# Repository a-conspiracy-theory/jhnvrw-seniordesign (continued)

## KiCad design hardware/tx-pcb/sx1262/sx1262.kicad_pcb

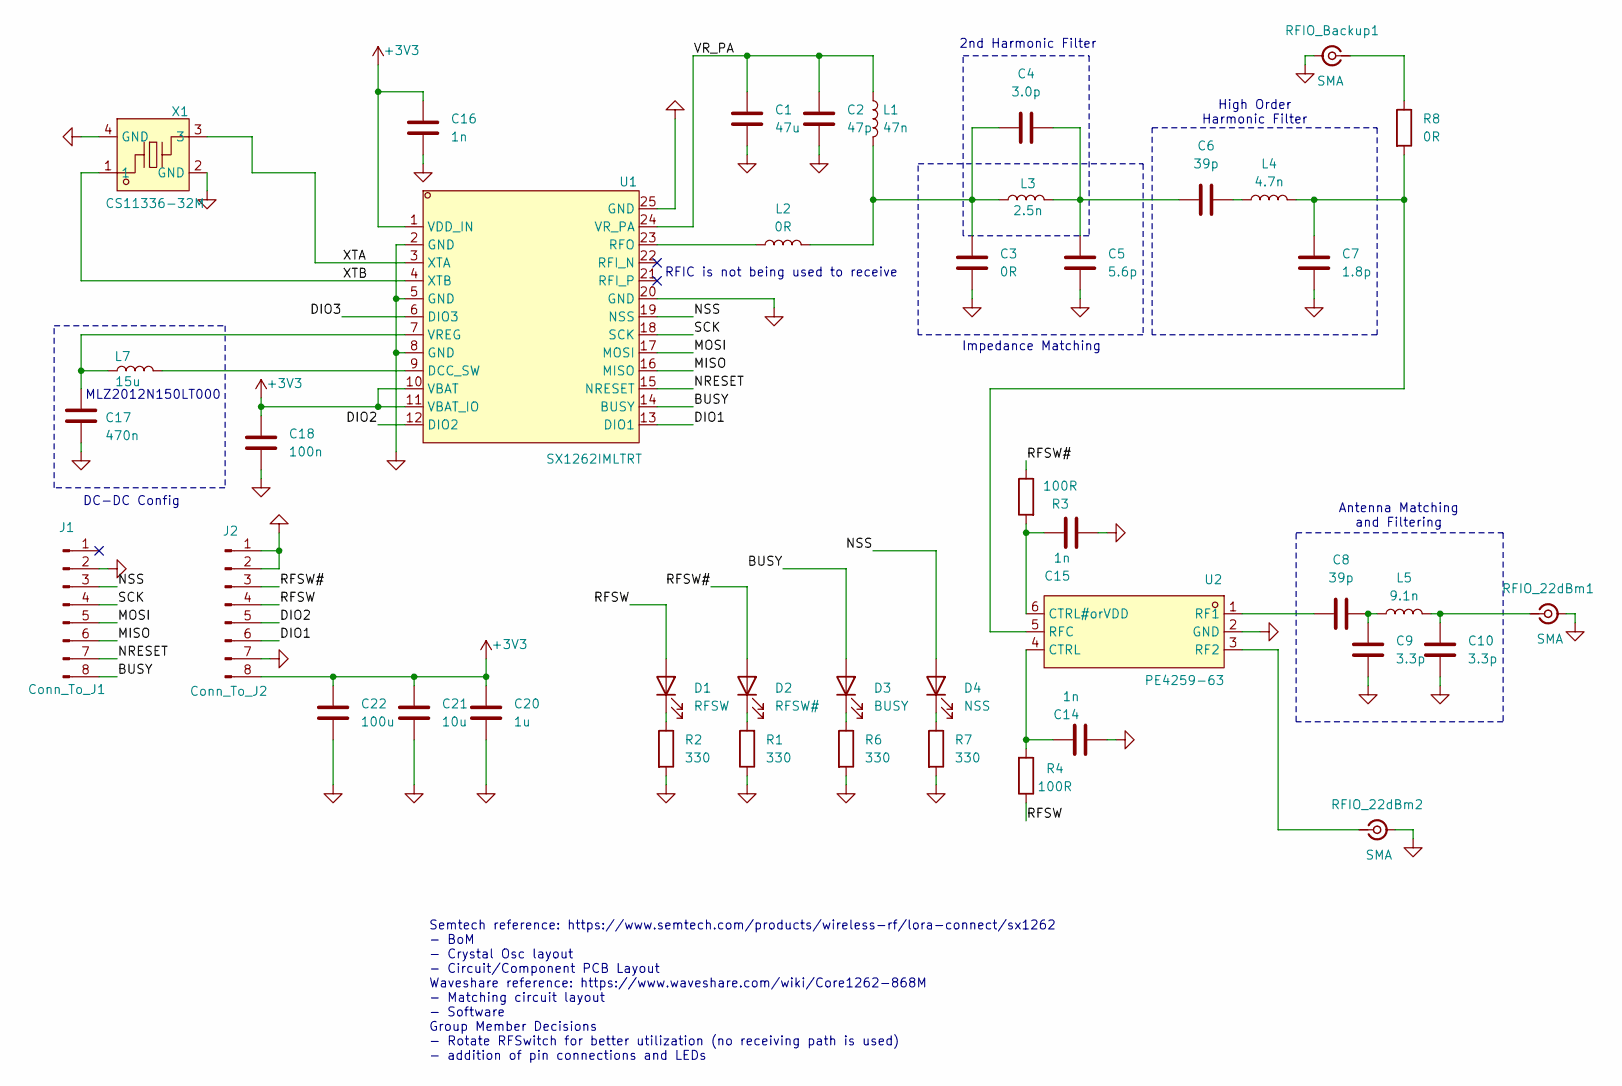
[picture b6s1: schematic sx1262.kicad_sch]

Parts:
C1: 47u; C_0805_2012Metric_Pad1.18x1.45mm_HandSolder
C2: 47p; C_0805_2012Metric_Pad1.18x1.45mm_HandSolder
C3: 0R; C_0805_2012Metric_Pad1.18x1.45mm_HandSolder
C4: 3.0p; C_0805_2012Metric_Pad1.18x1.45mm_HandSolder
C5: 5.6p; C_0805_2012Metric_Pad1.18x1.45mm_HandSolder
C6, C8: 39p; C_0805_2012Metric_Pad1.18x1.45mm_HandSolder
C7: 1.8p; C_0805_2012Metric_Pad1.18x1.45mm_HandSolder
C9, C10: 3.3p; C_0805_2012Metric_Pad1.18x1.45mm_HandSolder
C14, C15, C16: 1n; C_0805_2012Metric_Pad1.18x1.45mm_HandSolder
C17: 470n; C_0805_2012Metric_Pad1.18x1.45mm_HandSolder
C18: 100n; C_0805_2012Metric_Pad1.18x1.45mm_HandSolder
C20: 1u; C_0805_2012Metric_Pad1.18x1.45mm_HandSolder
C21: 10u; C_0805_2012Metric_Pad1.18x1.45mm_HandSolder
C22: 100u; C_0805_2012Metric_Pad1.18x1.45mm_HandSolder
D1: RFSW; LED_0805_2012Metric_Pad1.15x1.40mm_HandSolder
D2: RFSW#; LED_0805_2012Metric_Pad1.15x1.40mm_HandSolder
D3: BUSY; LED_0805_2012Metric_Pad1.15x1.40mm_HandSolder
D4: NSS; LED_0805_2012Metric_Pad1.15x1.40mm_HandSolder
J1: Conn_To_J1; PinHeader_1x08_P2.54mm_Vertical
J2: Conn_To_J2; PinHeader_1x08_P2.54mm_Vertical
L1: 47n; L_0805_2012Metric_Pad1.05x1.20mm_HandSolder
L2: 0R; L_0805_2012Metric_Pad1.05x1.20mm_HandSolder
L3: 2.5n; L_0805_2012Metric_Pad1.05x1.20mm_HandSolder
L4: 4.7n; L_0805_2012Metric_Pad1.05x1.20mm_HandSolder
L5: 9.1n; L_0805_2012Metric_Pad1.05x1.20mm_HandSolder
L7: 15u; L_0805_2012Metric_Pad1.05x1.20mm_HandSolder
R1, R2, R6, R7: 330; R_0805_2012Metric_Pad1.20x1.40mm_HandSolder
R3, R4: 100R; R_0805_2012Metric_Pad1.20x1.40mm_HandSolder
R8: 0R; R_0805_2012Metric_Pad1.20x1.40mm_HandSolder
RFIO_22dBm1, RFIO_22dBm2: SMA; SMA_Amphenol_901-143_Horizontal
RFIO_Backup1: SMA; SMA_Amphenol_901-143_Horizontal
U1: SX1262IMLTRT; QFN-24_L4.0-W4.0-P0.50-BL-EP2.6; MPN SX1262IMLTRT; LCSC Part C191341
U2: PE4259-63; SC-70-6_L2.2-W1.3-P0.65-LS2.1-BL; MPN PE4259-63; LCSC Part C470892
X1: CS11336-32M; NX2016SA_NDK; MPN Q22FA12800025; LCSC Part C187794

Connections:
+3V3: C16.1, C18.1, C20.1, C21.1, C22.1, J2.8, U1.1 (VDD_IN), U1.10 (VBAT), U1.11 (VBAT_IO)
/BUSY: D3.2 (A), J1.8, U1.14 (BUSY)
/DIO1: J2.6, U1.13 (DIO1)
/DIO2: J2.5, U1.12 (DIO2)
/DIO3: U1.6 (DIO3)
/MISO: J1.6, U1.16 (MISO)
/MOSI: J1.5, U1.17 (MOSI)
/NRESET: J1.7, U1.15 (NRESET)
/NSS: D4.2 (A), J1.3, U1.19 (NSS)
/RFSW: D1.2 (A), J2.4, R4.1
/RFSW#: D2.2 (A), J2.3, R3.1
/SCK: J1.4, U1.18 (SCK)
/VR_PA: C1.1, C2.1, L1.1, U1.24 (VR_PA)
/XTA: U1.3 (XTA), X1.3
/XTB: U1.4 (XTB), X1.1
GND: C1.2, C2.2, C3.2, C5.2, C7.2, C9.2, C10.2, C14.2, C15.2, C16.2, C17.2, C18.2, C20.2, C21.2, C22.2, J1.2, J2.1, J2.2, J2.7, R1.1, R2.2, R6.2, R7.2, RFIO_22dBm1.2 (Ext), RFIO_22dBm2.2 (Ext), RFIO_Backup1.2 (Ext), U1.2 (GND), U1.5 (GND), U1.8 (GND), U1.20 (GND), U1.25 (GND), U2.2 (GND), X1.2 (GND), X1.4 (GND)
unnamed: C3.1, C4.1, L1.2, L2.2, L3.1
unnamed: C4.2, C5.1, C6.1, L3.2
unnamed: C6.2, L4.1
unnamed: C8.2, C9.1, L5.1
unnamed: D1.1 (K), R2.1
unnamed: D2.1 (K), R1.2
unnamed: D3.1 (K), R6.1
unnamed: D4.1 (K), R7.1
unnamed: C10.1, L5.2, RFIO_22dBm1.1 (In)
unnamed: RFIO_22dBm2.1 (In), U2.3 (RF2)
unnamed: R8.1, RFIO_Backup1.1 (In)
unnamed: L7.2, U1.9 (DCC_SW)
unnamed: L2.1, U1.23 (RFO)
unnamed: C17.1, L7.1, U1.7 (VREG)
unnamed: C15.1, R3.2, U2.6 (CTRL#orVDD)
unnamed: C14.1, R4.2, U2.4 (CTRL)
unnamed: C8.1, U2.1 (RF1)
unnamed: C7.1, L4.2, R8.2, U2.5 (RFC)

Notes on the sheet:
RFIC is not being used to receive
MLZ2012N150LT000
High Order Harmonic Filter
2nd Harmonic Filter
DC-DC Config
Antenna Matching and Filtering
Impedance Matching
Semtech reference: https://www.semtech.com/products/wireless-rf/lora-connect/sx1262 - BoM - Crystal Osc layout - Circuit/Component PCB Layout Waveshare reference: https://www.waveshare.com/wiki/Core1262-868M - Matching circuit layout - Software Group Member Decisions - Rotate RFSwitch for better ut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

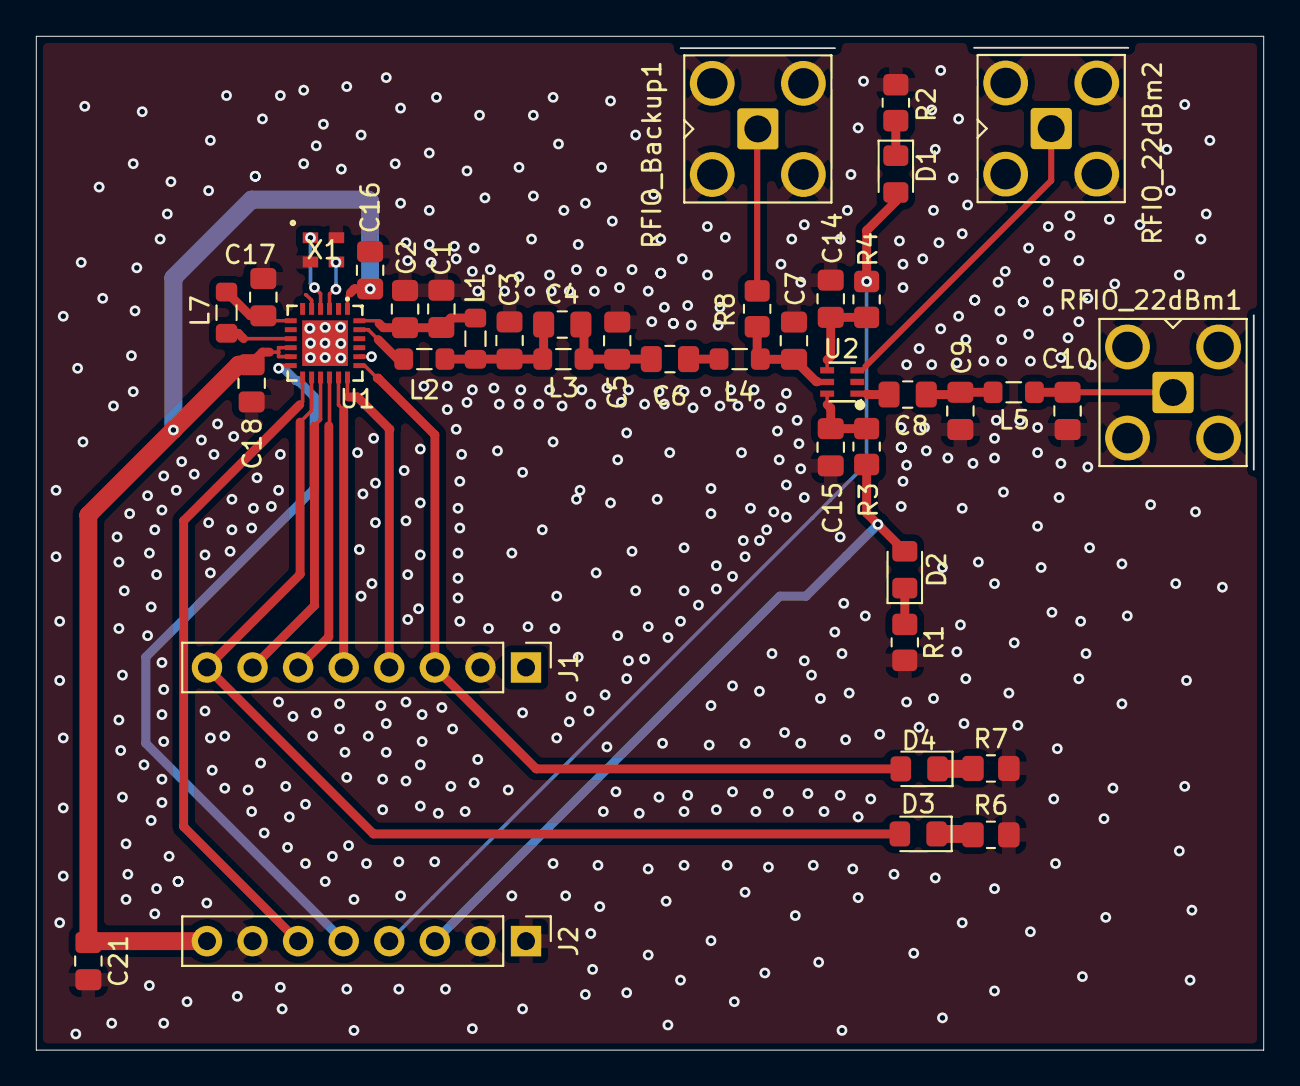
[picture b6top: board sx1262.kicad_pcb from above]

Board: 4 copper layers, 68.3 x 56.5 mm, 41 parts (0 on the bottom side), 33 nets.

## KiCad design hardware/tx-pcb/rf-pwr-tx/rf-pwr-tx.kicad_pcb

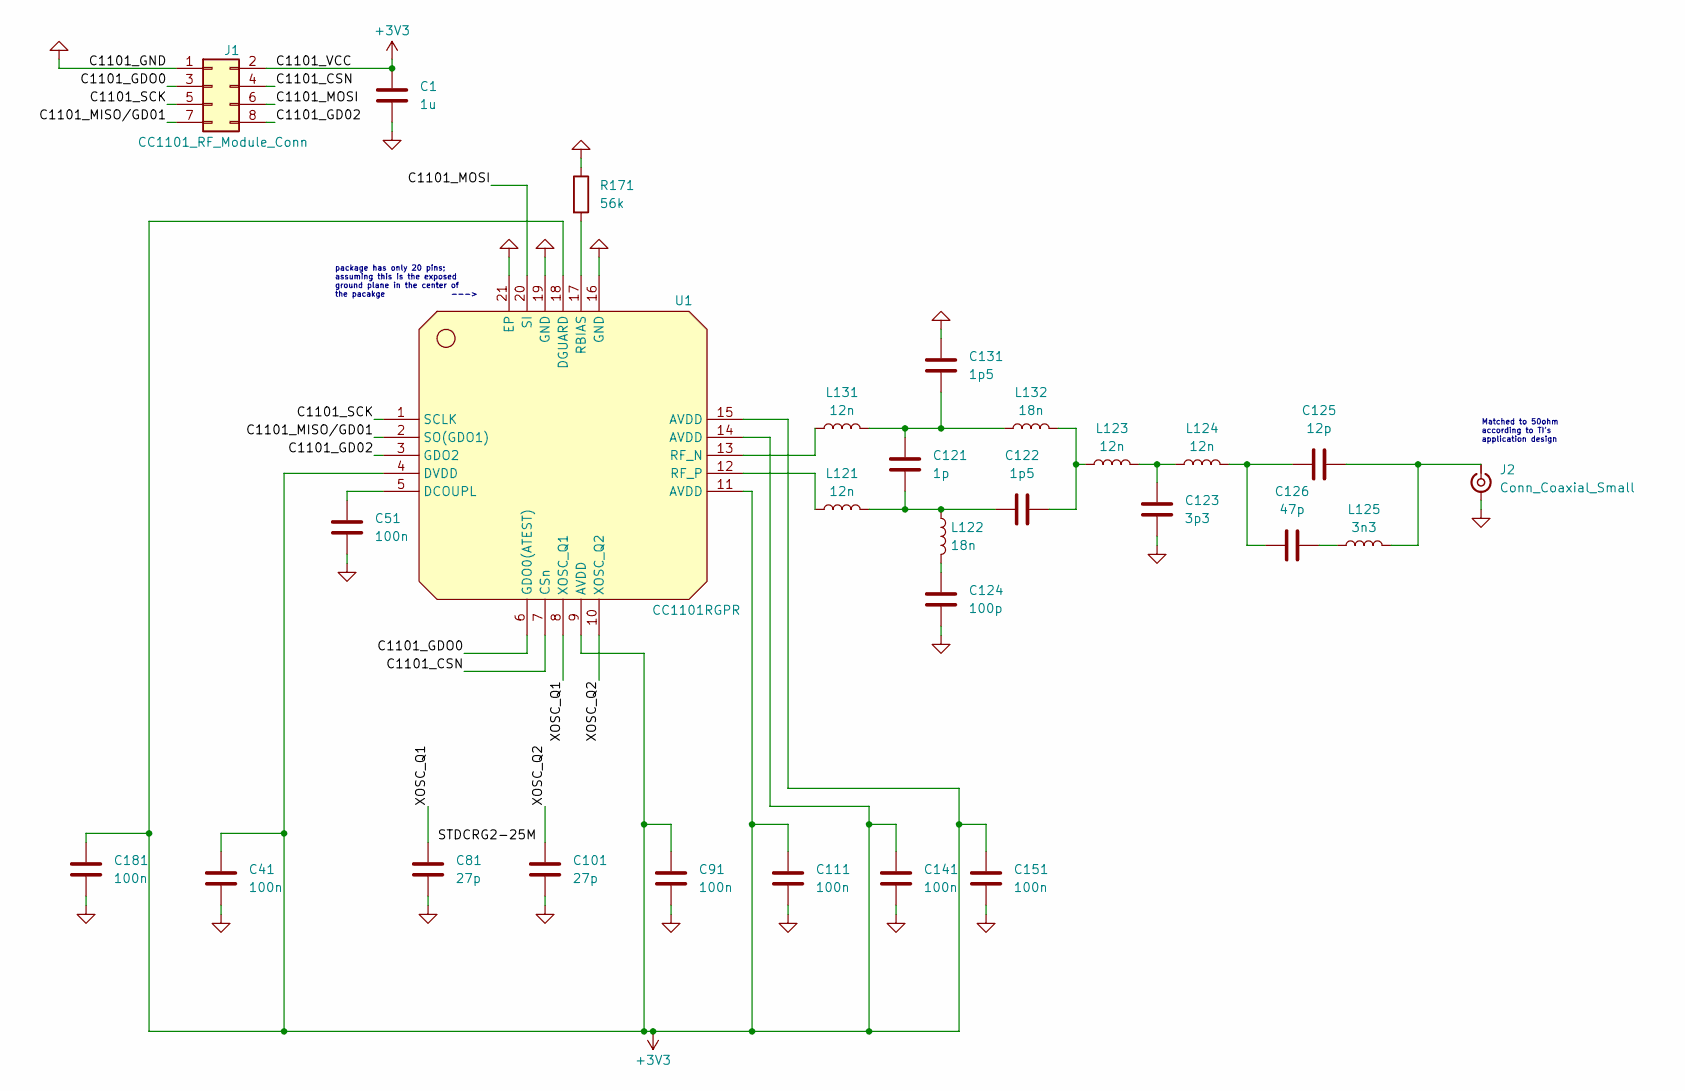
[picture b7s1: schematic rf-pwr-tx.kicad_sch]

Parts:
C1: 1u; C_0402_1005Metric_Pad0.74x0.62mm_HandSolder
C41, C51, C91, C111, C141, C151, C181: 100n; C_0402_1005Metric_Pad0.74x0.62mm_HandSolder
C81, C101: 27p; C_0402_1005Metric_Pad0.74x0.62mm_HandSolder
C121: 1p; C_0402_1005Metric_Pad0.74x0.62mm_HandSolder
C122, C131: 1p5; C_0402_1005Metric_Pad0.74x0.62mm_HandSolder
C123: 3p3; C_0402_1005Metric_Pad0.74x0.62mm_HandSolder
C124: 100p; C_0402_1005Metric_Pad0.74x0.62mm_HandSolder
C125: 12p; C_0402_1005Metric_Pad0.74x0.62mm_HandSolder
C126: 47p; C_0402_1005Metric_Pad0.74x0.62mm_HandSolder
J1: CC1101_RF_Module_Conn; PinSocket_2x04_P2.54mm_Vertical
J2: Conn_Coaxial_Small; SMA_Amphenol_901-143_Horizontal
L121, L123, L124, L131: 12n; L_0402_1005Metric_Pad0.77x0.64mm_HandSolder
L122, L132: 18n; L_0402_1005Metric_Pad0.77x0.64mm_HandSolder
L125: 3n3; L_0402_1005Metric_Pad0.77x0.64mm_HandSolder
R171: 56k; R_0402_1005Metric_Pad0.72x0.64mm_HandSolder
U1: CC1101RGPR; RGP20_2P4X2P4; MPN CC1101RGPR; LCSC Part C29953

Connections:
+3V3: C1.1, C41.1, C91.1, C111.1, C141.1, C151.1, C181.1, J1.2, U1.4 (DVDD), U1.9 (AVDD), U1.11 (AVDD), U1.14 (AVDD), U1.15 (AVDD), U1.18 (DGUARD)
/C1101_CSN: J1.4, U1.7 (CSn)
/C1101_GD02: J1.8, U1.3 (GDO2)
/C1101_GDO0: J1.3, U1.6 (GDO0(ATEST))
/C1101_MISO/GD01: J1.7, U1.2 (SO(GDO1))
/C1101_MOSI: J1.6, U1.20 (SI)
/C1101_SCK: J1.5, U1.1 (SCLK)
/XOSC_Q1: C81.1, U1.8 (XOSC_Q1)
/XOSC_Q2: C101.1, U1.10 (XOSC_Q2)
GND: C1.2, C41.2, C51.2, C81.2, C91.2, C101.2, C111.2, C123.1, C124.2, C131.1, C141.2, C151.2, C181.2, J1.1, J2.2 (Ext), R171.1, U1.16 (GND), U1.19 (GND), U1.21 (EP)
unnamed: C121.1, C131.2, L131.2, L132.1
unnamed: C121.2, C122.1, L121.2, L122.1
unnamed: C122.2, L123.1, L132.2
unnamed: C123.2, L123.2, L124.1
unnamed: C124.1, L122.2
unnamed: C125.1, C126.1, L124.2
unnamed: C126.2, L125.1
unnamed: C125.2, J2.1 (In), L125.2
unnamed: C51.1, U1.5 (DCOUPL)
unnamed: R171.2, U1.17 (RBIAS)
unnamed: L131.1, U1.13 (RF_N)
unnamed: L121.1, U1.12 (RF_P)

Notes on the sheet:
Matched to 50ohm according to TI's application design
package has only 20 pins; assuming this is the exposed ground plane in the center of the pacakge --->

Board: 2 copper layers, 28 parts (0 on the bottom side), 22 nets, no tracks yet.

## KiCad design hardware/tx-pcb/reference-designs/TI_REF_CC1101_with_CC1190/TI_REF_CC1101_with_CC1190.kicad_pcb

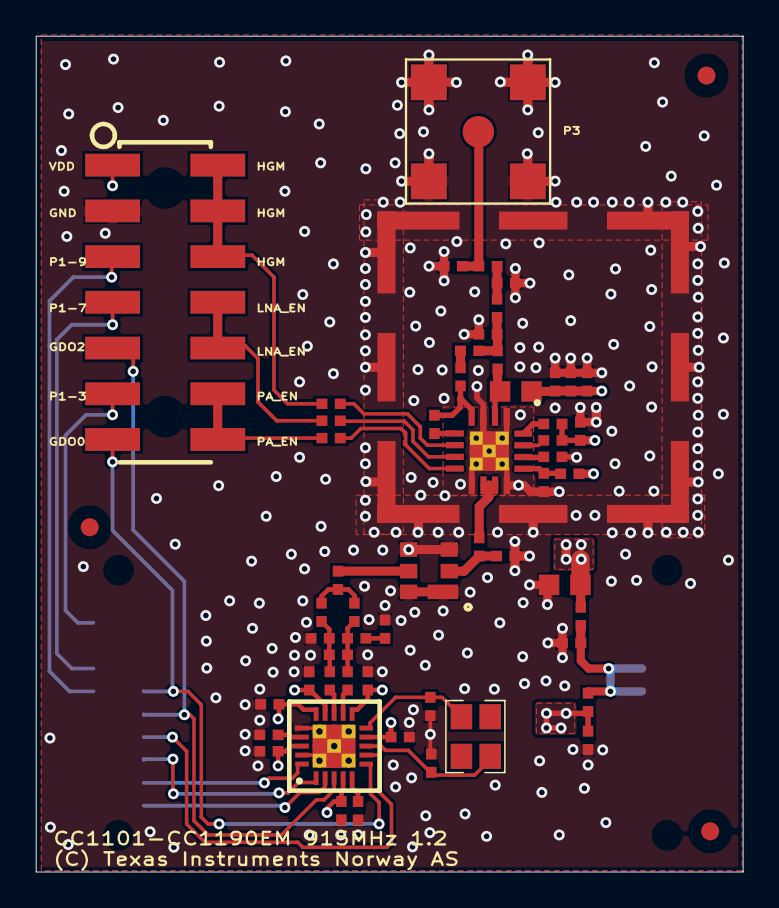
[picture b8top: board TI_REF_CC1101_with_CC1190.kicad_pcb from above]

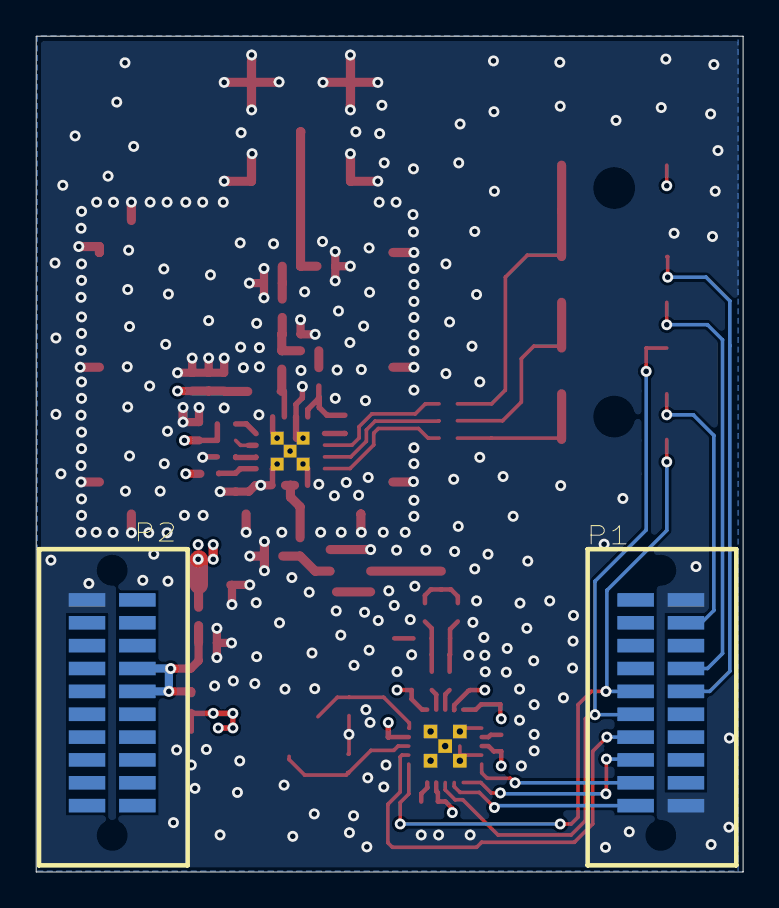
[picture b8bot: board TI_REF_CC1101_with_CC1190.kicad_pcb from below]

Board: 4 copper layers, 39.3 x 46.4 mm, 60 parts (2 on the bottom side), 43 nets.

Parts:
C1, C30: C_1U_0402_X5R_K_6P3; 0402 (REFLOW LF)
C2: C_10U_0603_X5R_M_4; 0603 (REFLOW)
C3: C_220P_0402_NP0_J_50; 0402 (REFLOW LF)
C21, C26, C123: C_47P_0402_NP0_J_50; 0402 (REFLOW LF)
C22, C52, C81: C_12P_0402_NP0_J_50; 0402 (REFLOW LF)
C24: C_3P3_0402_NP0_C_50; 0402 (REFLOW LF)
C25: C_7P5_0402_NP0_C_50; 0402 (REFLOW LF)
C27: C_1N_0402_NP0_J_50; 0402 (REFLOW LF)
C28: C_0402; 0402 (REFLOW LF)
C41, C51, C91, C111, C141, C151, C181: C_100N_0402_X5R_K_10; 0402 (REFLOW LF)
C101, C132: C_15P_0402_NP0_J_50; 0402 (REFLOW LF)
C121: C_1P0_0402_NP0_C_50; 0402 (REFLOW LF)
C122, C131: C_1P5_0402_NP0_C_50; 0402 (REFLOW LF)
C124: C_100P_0402_NP0_J_50; 0402 (REFLOW LF)
C125: C_0P8_0402_NP0_B_50; 0402 (REFLOW LF)
C161: C_27P_0402_NP0_J_50; 0402 (REFLOW LF)
FM1, FM2, FM3: FIDUCIAL_MARK_1MM; FIDUCAL_MARK_1mm
L1: L_BEAD_102_0402; 0402 (REFLOW LF)
L2: L_11N_0402_J_LQW; 0402 (REFLOW LF)
L21: L_22N_0603_J_LQW; 0603 (REFLOW)
L22: L_7N5_0402_G_LQW; 0402 (REFLOW LF)
L23: L_2N9_0402_B_LQW; 0402 (REFLOW LF)
L24: L_9N1_0402_G_LQW; 0402 (REFLOW LF)
L25: L_10N_0402_G_LQW; 0402 (REFLOW LF)
L121, L131: L_12N_0402_J_LQW; 0402 (REFLOW LF)
L122, L132: L_18N_0402_J_LQW; 0402 (REFLOW LF)
L130: L_1N5_0402_S; 0402 (REFLOW LF)
P1, P2: SMD_SOCKET_2X10; SFM SMD Socket 2x10
P3: SMA_SMD; SMA_SMD (Note_recommended)
P4: PINROW_SMD_2X7_2.54MM_PEG; PINROW_SMD_2X7_2.54MM_PEG (Gradconn BB02-HP)
P5: SHIELD BMIS-202; Shield_BMIS-202
R3, R4, R5: R_10K_0402_F; 0402 (REFLOW LF)
R141: R_3K3_0402_F; 0402 (REFLOW LF)
R151: R_47_0402_G; 0402 (REFLOW LF)
R161: R_10_0402_G; 0402 (REFLOW LF)
R171: R_56K_0402_F; 0402 (REFLOW LF)
U1: CC1101; QLP20_DATASHEET (QLP20)
U2: CC1190_DATASHEET; QFN16_4_4_DATASHEET (CC1190)
U3: EPCOS_B3588; Epcos_B3588
X1: X_26.000/20/40/40/10; XTAL_SMD_3_2x2_5 (3.2 x 2.5 mm)

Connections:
CSn: P1.14, U1.7
GDO0: P1.10, P4.13, U1.6
GDO2: P1.12, P4.9, U1.3
GND: C1.2, C2.2, C3.2, C24.1, C25.1, C26.2, C27.2, C28.1, C30.2, C41.2, C51.2, C81.2, C91.2, C101.2, C111.2, C124.1, C125.1, C131.2, C132.2, C141.2, C151.2, C161.2, C181.2, P1.1, P1.19, P2.2, P3.2, P3.3, P3.4, P3.5, P4.3, P5.1, P5.2, P5.3, P5.4, P5.5, P5.6, P5.7, P5.8, P5.9, P5.10, P5.11, P5.12, R141.1, R171.2, U1.16, U1.19, U1.21, U1.22, U1.23, U1.24, U1.25, U1.26, U1.27, U1.28, U2.1, U2.3, U2.9, U2.12, U2.17, U2.18, U2.19, U2.20, U2.21, U2.22, U2.23, U2.24, U3.1, U3.3, U3.4, U3.6
HGM: R3.2, U2.6
LNA_EN: R4.2, U2.7
unnamed: C21.2, C24.2, L22.2, L23.2
unnamed: C22.2, L22.1
unnamed: C52.1, U2.5
unnamed: C22.1, C52.2, U2.4
unnamed: C101.1, U1.10, X1.3
unnamed: C122.2, C123.1, L132.1
unnamed: C124.2, L122.2
unnamed: C125.2, L25.1, U3.2
unnamed: C121.2, C131.1, L131.2, L132.2
unnamed: C28.2, L24.1, P3.1
unnamed: C25.2, L23.1, L24.2
unnamed: L25.2, U2.10, U2.11
unnamed: C121.1, C122.1, L121.2, L122.1
unnamed: P1.3, P4.11
unnamed: P1.7, P4.7
unnamed: P1.9, P4.5
unnamed: P4.2, P4.4, P4.6, R3.1
unnamed: P4.12, P4.14, R5.1
unnamed: P4.8, P4.10, R4.1
unnamed: R141.2, U2.14
unnamed: R151.2, U2.15
unnamed: R161.2, U2.16
unnamed: R171.1, U1.17
unnamed: C51.1, U1.5
unnamed: L121.1, U1.12
unnamed: L131.1, U1.13
unnamed: C21.1, L21.1, U2.2
unnamed: C132.1, L130.1, U2.13
unnamed: C123.2, U3.5
unnamed: C81.1, U1.8, X1.1
PA_EN: R5.2, U2.8
SCLK: P1.16, U1.1
SI: P1.18, U1.20
SO: P1.20, U1.2
VDD: C3.1, L1.2, L2.1, P2.7, P2.9
VDD_CC1101: C1.1, C41.1, C91.1, C111.1, C141.1, C151.1, C181.1, L1.1, U1.4, U1.9, U1.11, U1.14, U1.15, U1.18
VDD_CC1190: C2.1, C26.1, C27.1, C30.1, C161.1, L2.2, L21.2, L130.2, P4.1, R151.1, R161.1

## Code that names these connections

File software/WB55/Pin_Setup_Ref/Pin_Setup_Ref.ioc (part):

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Mcu.Name=STM32WB55CCUx
Mcu.Package=UFQFPN48
Mcu.UserName=STM32WB55CCUx
PA0.GPIOParameters=GPIO_Label
PA0.GPIO_Label=SX1262_DIO1
PA0.Signal=GPIO_Output
PA1.Mode=Full_Duplex_Master
PA1.Signal=SPI1_SCK
PA10.Mode=Asynchronous
PA10.Signal=USART1_RX
PA13.Mode=Serial_Wire
PA13.Signal=SYS_JTMS-SWDIO
PA14.Mode=Serial_Wire
PA14.Signal=SYS_JTCK-SWCLK
PA15.GPIOParameters=GPIO_Label
PA15.GPIO_Label=BTN5
PA15.Signal=GPIO_Output
PA2.GPIOParameters=GPIO_Label
PA2.GPIO_Label=SX1262_BUSY
PA2.Signal=GPIO_Input
PA3.GPIOParameters=GPIO_Label
PA3.GPIO_Label=SX1262_DIO2
PA3.Signal=GPIO_Output
PA4.GPIOParameters=GPIO_Label
PA4.GPIO_Label=SX1262_RST
PA4.Signal=GPIO_Output
PA5.GPIOParameters=GPIO_Label
PA5.GPIO_Label=SX1262_RFSW
PA5.Signal=GPIO_Output
PA6.Mode=Full_Duplex_Master
PA6.Signal=SPI1_MISO
PA7.Mode=Full_Duplex_Master
PA7.Signal=SPI1_MOSI
PA9.Mode=Asynchronous
PA9.Signal=USART1_TX
PB2.Mode=NSS_Signal_Hard_Input
PB2.Signal=SPI1_NSS
PB3.GPIOParameters=GPIO_Label
PB3.GPIO_Label=BTN2
PB3.Signal=GPIO_Input
PB4.GPIOParameters=GPIO_Label
PB4.GPIO_Label=BTN1
PB4.Signal=GPIO_Input
PB5.GPIOParameters=GPIO_Label
PB5.GPIO_Label=BTN3
PB5.Signal=GPIO_Input
PB6.GPIOParameters=GPIO_Label
PB6.GPIO_Label=BTN4
PB6.Signal=GPIO_Input
PB7.GPIOParameters=GPIO_Label
PB7.GPIO_Label=SX1262_RFSW\#
PB7.Signal=GPIO_Input
PB8.Mode=I2C
PB8.Signal=I2C1_SCL
PB9.Mode=I2C
PB9.Signal=I2C1_SDA
PC14-OSC32_IN.Mode=LSE-External-Oscillator
PC14-OSC32_IN.Signal=RCC_OSC32_IN
PC15-OSC32_OUT.Mode=LSE-External-Oscillator
PC15-OSC32_OUT.Signal=RCC_OSC32_OUT
RCC.HSE_VALUE=8000000
board=custom

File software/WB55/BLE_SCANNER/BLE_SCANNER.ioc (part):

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Mcu.Name=STM32WB55CEUx
Mcu.Package=UFQFPN48
Mcu.UserName=STM32WB55CEUx
PA0.GPIOParameters=GPIO_Label
PA0.GPIO_Label=SX1262_DIO1
PA0.Signal=GPXTI0
PA1.Mode=Full_Duplex_Master
PA1.Signal=SPI1_SCK
PA10.Signal=USART1_RX
PA15.GPIOParameters=GPIO_Label
PA15.GPIO_Label=BTN5
PA15.Signal=GPIO_Output
PA2.GPIOParameters=GPIO_Label
PA2.GPIO_Label=SX1262_BUSY
PA2.Signal=GPIO_Input
PA3.GPIOParameters=GPIO_Label
PA3.GPIO_Label=SX1262_DIO2_CPS
PA3.Signal=GPIO_Output
PA4.GPIOParameters=GPIO_Label
PA4.GPIO_Label=SX1262_RST
PA4.Signal=GPIO_Output
PA5.GPIOParameters=GPIO_Label
PA5.GPIO_Label=SX1262_TXEN
PA5.Signal=GPIO_Output
PA6.Mode=Full_Duplex_Master
PA6.Signal=SPI1_MISO
PA7.Mode=Full_Duplex_Master
PA7.Signal=SPI1_MOSI
PB2.GPIOParameters=GPIO_Label
PB2.GPIO_Label=SX1262_NSS
PB2.Signal=GPIO_Output
PB3.GPIOParameters=GPIO_Label
PB3.GPIO_Label=BTN2
PB3.Signal=GPIO_Input
PB4.GPIOParameters=GPIO_Label
PB4.GPIO_Label=BTN1
PB4.Signal=GPIO_Input
PB5.GPIOParameters=GPIO_Label
PB5.GPIO_Label=BTN3
PB5.Signal=GPIO_Output
PB6.GPIOParameters=GPIO_Label
PB6.GPIO_Label=BTN4
PB6.Signal=GPIO_Input
PB7.GPIOParameters=GPIO_Label
PB7.GPIO_Label=SX1262_RXEN
PB7.Signal=GPIO_Output
PB8.Mode=I2C
PB8.Signal=I2C1_SCL
PB9.Mode=I2C
PB9.Signal=I2C1_SDA
PC14-OSC32_IN.Mode=LSE-External-Oscillator
PC14-OSC32_IN.Signal=RCC_OSC32_IN
PC15-OSC32_OUT.Mode=LSE-External-Oscillator
PC15-OSC32_OUT.Signal=RCC_OSC32_OUT
RCC.HSE_VALUE=32000000
RCC.SYSCLKFreq_VALUE=32000000
RCC.SYSCLKSource=RCC_SYSCLKSOURCE_HSE
board=custom

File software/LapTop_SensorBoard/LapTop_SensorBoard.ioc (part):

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Mcu.Name=STM32WB05KZVx
Mcu.Package=VFQFPN32
Mcu.UserName=STM32WB05KZVx
PA0.TagName=B1
PA1.TagName=VCP_TX
PA9.Mode=Asynchronous
PA9.Signal=USART1_TX
PB0.Mode=Asynchronous
PB0.Signal=USART1_RX
PB0.TagName=VCP_RX
PB1.Signal=S_TIM2_ETR
PB1.TagName=LD1
PB12.Mode=LSE-External-Oscillator
PB12.Signal=RCC_OSC32_OUT
PB13.Mode=LSE-External-Oscillator
PB13.Signal=RCC_OSC32_IN
PB14.TagName=B3
PB2.Mode=CTS_RTS
PB2.Signal=USART1_RTS
PB2.TagName=LD3
PB3.Mode=CTS_RTS
PB3.Signal=USART1_CTS
PB4.TagName=LD2
PB5.TagName=B2
PB6.Mode=I2C
PB6.Signal=I2C1_SCL
PB7.Mode=I2C
PB7.Signal=I2C1_SDA
RCC.HSE_VALUE=32000000
board=NUCLEO-WB05KZ
boardIOC=true

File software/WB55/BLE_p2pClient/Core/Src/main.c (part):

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  __HAL_RCC_GPIOB_CLK_ENABLE();
  __HAL_RCC_GPIOA_CLK_ENABLE();

  /*Configure GPIO pin Output Level */
  HAL_GPIO_WritePin(GPIOA, SX1262_TXEN_Pin|SX1262_RST_Pin, GPIO_PIN_RESET);

  /*Configure GPIO pin Output Level */
  HAL_GPIO_WritePin(SX1262_NSS_GPIO_Port, SX1262_NSS_Pin, GPIO_PIN_SET);

  /*Configure GPIO pin Output Level */
  HAL_GPIO_WritePin(SX1262_RXEN_GPIO_Port, SX1262_RXEN_Pin, GPIO_PIN_RESET);

  /*Configure GPIO pin Output Level */
  HAL_GPIO_WritePin(GPIOB, GPIO_PIN_3|GPIO_PIN_4, GPIO_PIN_RESET);

  /*Configure GPIO pin : PH3 */
  GPIO_InitStruct.Pin = GPIO_PIN_3;
  GPIO_InitStruct.Mode = GPIO_MODE_AF_PP;
  GPIO_InitStruct.Pull = GPIO_NOPULL;
  GPIO_InitStruct.Speed = GPIO_SPEED_FREQ_LOW;
  HAL_GPIO_Init(GPIOH, &GPIO_InitStruct);

  /*Configure GPIO pins : SX1262_TXEN_Pin SX1262_NSS_Pin SX1262_RST_Pin */
  GPIO_InitStruct.Pin = SX1262_TXEN_Pin|SX1262_NSS_Pin|SX1262_RST_Pin;
  GPIO_InitStruct.Mode = GPIO_MODE_OUTPUT_PP;
  GPIO_InitStruct.Pull = GPIO_NOPULL;
  GPIO_InitStruct.Speed = GPIO_SPEED_FREQ_LOW;
  HAL_GPIO_Init(GPIOA, &GPIO_InitStruct);

  /*Configure GPIO pin : SX1262_BUSY_Pin */
  GPIO_InitStruct.Pin = SX1262_BUSY_Pin;
  GPIO_InitStruct.Mode = GPIO_MODE_INPUT;
  GPIO_InitStruct.Pull = GPIO_NOPULL;
  HAL_GPIO_Init(SX1262_BUSY_GPIO_Port, &GPIO_InitStruct);

  /*Configure GPIO pin : SX1262_DIO1_Pin */
  GPIO_InitStruct.Pin = SX1262_DIO1_Pin;
  GPIO_InitStruct.Mode = GPIO_MODE_IT_RISING;
  GPIO_InitStruct.Pull = GPIO_NOPULL;
  HAL_GPIO_Init(SX1262_DIO1_GPIO_Port, &GPIO_InitStruct);

  /*Configure GPIO pin : SX1262_RXEN_Pin */
  GPIO_InitStruct.Pin = SX1262_RXEN_Pin;
  GPIO_InitStruct.Mode = GPIO_MODE_OUTPUT_PP;
  GPIO_InitStruct.Pull = GPIO_NOPULL;
  GPIO_InitStruct.Speed = GPIO_SPEED_FREQ_LOW;
  HAL_GPIO_Init(SX1262_RXEN_GPIO_Port, &GPIO_InitStruct);

  /*Configure GPIO pins : PB3 PB4 */
  GPIO_InitStruct.Pin = GPIO_PIN_3|GPIO_PIN_4;
  GPIO_InitStruct.Mode = GPIO_MODE_OUTPUT_PP;
  GPIO_InitStruct.Pull = GPIO_NOPULL;
  GPIO_InitStruct.Speed = GPIO_SPEED_FREQ_LOW;
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
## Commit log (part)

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2026-05-26 initial commit. created base rx-pcb kicad file
2026-05-26 folder restructuring
2026-05-26 added base tx-pcb kicad project
2026-05-30 RF work start
2026-06-01 minor board updates. added the MLPF-WB chip for stm impedance matching
2026-06-02 finished initial board. no sensors or power harvesting, but its programmable and bluetooth should work.
2026-06-06 updated bluetooth section to be in-line with filter datasheet. rearranged LFEX to allow I2C connection.
2026-06-09 finished V1 of receiver PCB. No power electronics yet.
2026-06-17 separated bluetooth and harvesting boards
2026-06-17 fixed deletion of some files in the GIT
2026-06-17 began the power harvesting board
2026-06-23 WIP TX Board
2026-06-23 fixed pwr header silkscreen mismatch. added reverse bias protection diode. added power good indicator diode for testing (DNP on final iteration)
2026-06-26 began work on RF daughter board; included TI Reference designs
2026-06-26 First nick commit test
